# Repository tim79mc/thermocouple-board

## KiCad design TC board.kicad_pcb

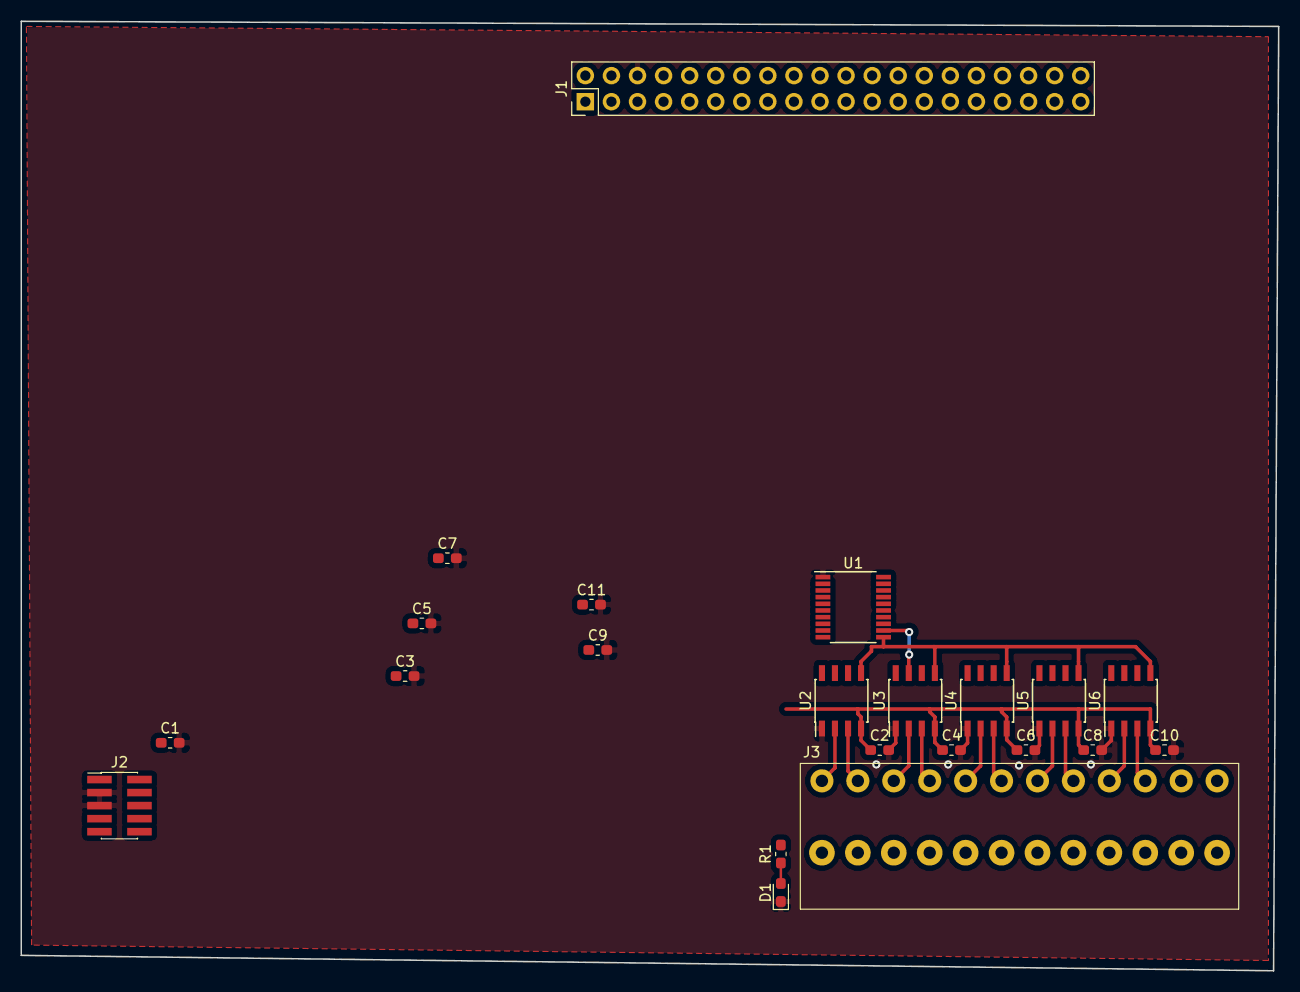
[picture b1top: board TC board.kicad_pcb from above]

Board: 2 copper layers, 122.5 x 92.5 mm, 22 parts (0 on the bottom side), 25 nets.

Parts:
C1, C5, C7: 100nF; C_0603_1608Metric_Pad1.05x0.95mm_HandSolder
C2, C4, C6, C8, C10: 0.1uF; C_0603_1608Metric_Pad1.05x0.95mm_HandSolder
C3: 4.7uF; C_0603_1608Metric_Pad1.05x0.95mm_HandSolder
C9: 10nF; C_0603_1608Metric_Pad1.05x0.95mm_HandSolder
C11: 1uF; C_0603_1608Metric_Pad1.05x0.95mm_HandSolder
D1: GREEN; LED_0603_1608Metric_Pad1.05x0.95mm_HandSolder
J1: Raspberry_Pi_2_3; PinHeader_2x20_P2.54mm_Vertical
J2: Conn_ARM_JTAG_SWD_10; PinHeader_2x05_P1.27mm_Vertical_SMD
J3: Screw_Terminal_01x12; TBLH10-350-12
R1: 680R; R_0603_1608Metric_Pad1.05x0.95mm_HandSolder
U1: STM32F038F6Px; TSSOP-20_4.4x6.5mm_P0.65mm
U2, U3, U4, U5, U6: MAX31855KASA; SOIC-8_3.9x4.9mm_P1.27mm

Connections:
+3V3: C2.1, C3.1, C4.1, C5.1, C6.1, C7.1, C8.1, C9.1, C10.1, C11.1, J1.1, J2.1, R1.1, U1.5, U1.16, U2.4, U3.4, U4.4, U5.4, U6.4
GND: C1.2, C2.2, C3.2, C4.2, C5.2, C6.2, C7.2, C8.2, C9.2, C10.2, C11.2, D1.1, J1.6, J2.3, J2.5, U1.1, U1.15, U2.1, U3.1, U4.1, U5.1, U6.1
I2C_SCL: J1.5, U1.17
I2C_SDA: J1.3, U1.18
NRST: C1.1, J2.10, U1.4
unnamed: D1.2, R1.2
SPI_CLK: U1.11, U2.5, U3.5, U4.5, U5.5, U6.5
SPI_MISO: U1.12, U2.7, U3.7, U4.7, U5.7, U6.7
SWDCLK: J2.4, U1.20
SWDIO: J2.2, U1.19
TC1+: J3.2, U2.3
TC1-: J3.1, U2.2
TC1_CS: U1.6, U2.6
TC2+: J3.4, U3.3
TC2-: J3.3, U3.2
TC2_CS: U1.7, U3.6
TC3+: J3.6, U4.3
TC3-: J3.5, U4.2
TC3_CS: U1.8, U4.6
TC4+: J3.8, U5.3
TC4-: J3.7, U5.2
TC4_CS: U1.9, U5.6
TC5+: J3.10, U6.3
TC5-: J3.9, U6.2
TC5_CS: U1.10, U6.6
